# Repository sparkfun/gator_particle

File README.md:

SparkFun gator:particle - micro:bit Accessory Board
=============================

[*SparkFun gator:particle - micro:bit Accessory Board (SEN-15271)*](https://www.sparkfun.com/products/15271)

An I<sup>2</sup>C sensor for detecting particles. Additionaly, the MAX30102 sensor can also be used for measure heart-rate and SpO<sub>2</sub> using special algorithms. These algorithms have limited functionality and are primarily meant for demonstration purposed.

*Example of pulse measurement:*

Instead of using pin connections or requiring soldering, this product provides connection pads for a more kid freindly experience with alligator clips. The design intention of this product is to be used with the [gato:bit (v2)](https://www.sparkfun.com/products/15162), and the [micro:bit development board](https://www.sparkfun.com/products/14208).

Repository Contents
-------------------

* **/Hardware** - Eagle design files (.brd, .sch)
* **/Production** - Production panel files (.brd)

Documentation
--------------
* **[Hookup Guide](https://learn.sparkfun.com/tutorials/sparkfun-gatorparticle-hookup-guide)** - Basic hookup guide for the gator:particle.
* **[gator:particle PXT Package](https://github.com/sparkfun/pxt-gator-particle)** - PXT- package for the MakeCode gator:particle extension.

License Information
-------------------

This product is _**open source**_! 

Please review the LICENSE.md file for license information. 

If you have any questions or concerns on licensing, please visit the [SparkFun Forum](https://forum.sparkfun.com/index.php) and post a topic. For more general questions related to our gator boards, please visit this section of the forum: [Gator Products](https://forum.sparkfun.com/viewforum.php?f=162).

Distributed as-is; no warranty is given.

- Your friends at SparkFun.

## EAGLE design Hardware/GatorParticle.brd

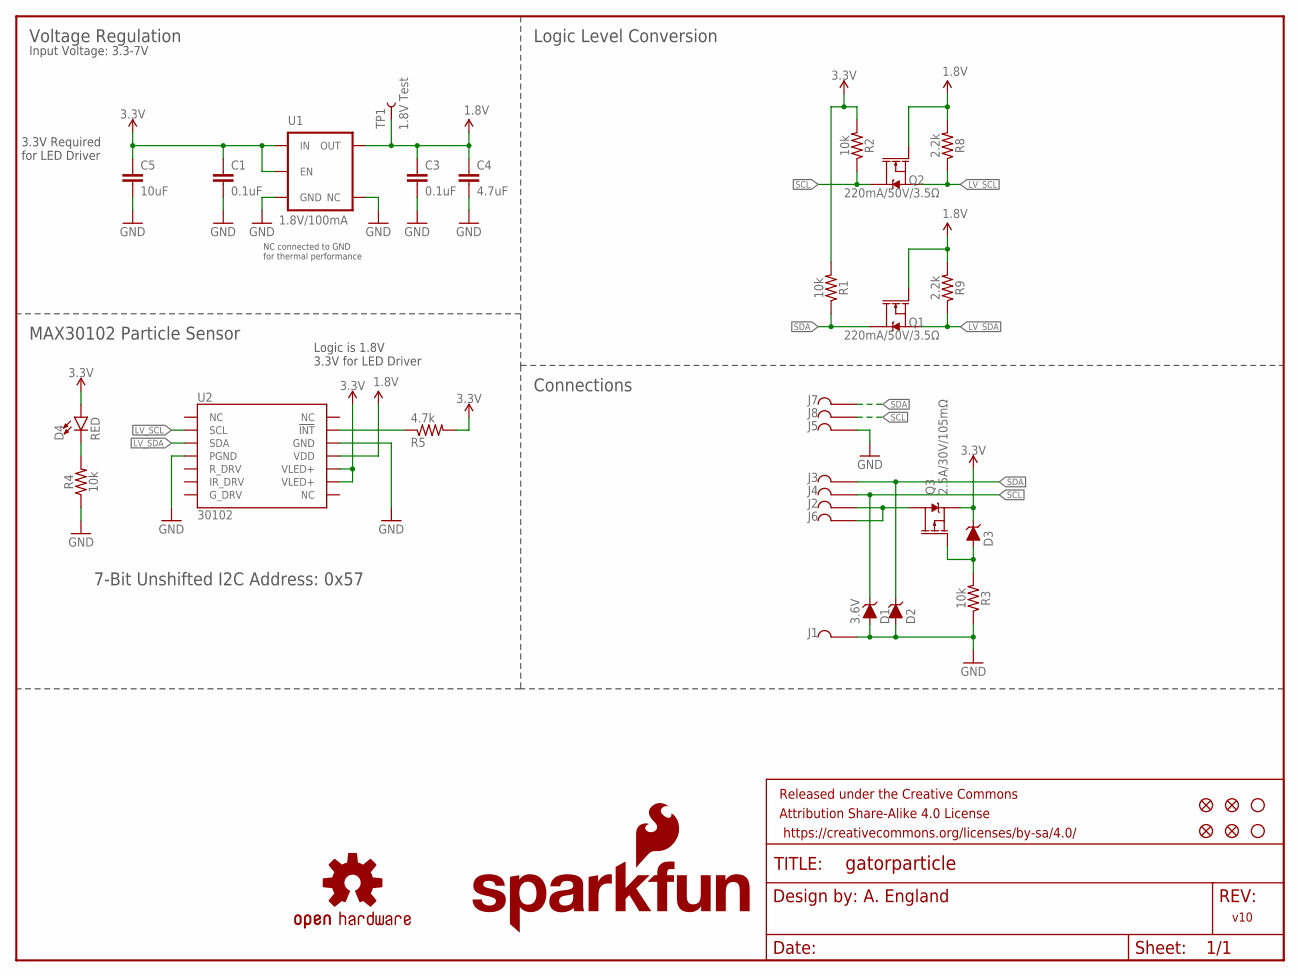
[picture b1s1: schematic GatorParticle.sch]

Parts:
C1, C3: 0.1uF; 0603
C4: 4.7uF; 0603
C5: 10uF; 0603
D1, D2, D3: 3.6V; SOD-323
D4: RED; LED-0603
FID1, FID2, FID3, FID4: FIDUCIALUFIDUCIAL; FIDUCIAL-MICRO
FRAME1: FRAME-LETTER; CREATIVE_COMMONS
J1, J2, J3, J4, J5, J6, J7, J8: GATORGATOR_MINI; GATOR_MINI
LOGO1: SFE_LOGO_NAME_FLAME.1_INCH; SFE_LOGO_NAME_FLAME_.1
LOGO2: OSHW-LOGOS; OSHW-LOGO-S
Q1, Q2: 220mA/50V/3.5Ω; SOT23-3
Q3: 2.5A/30V/105mΩ; SOT23-3
R1, R2, R3, R4: 10k; 0603
R5: 4.7k; 0603
R8, R9: 2.2k; 0603
STANDOFF2, STANDOFF3: STAND-OFFTIGHT; STAND-OFF-TIGHT
TP1: 1.8V Test; PAD.03X.04
U1: 1.8V/100mA; SC70
U2: 30102; OLGA-14

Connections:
1.8V: C3.1, C4.1, Q1.1 (G), Q2.1 (G), R8.2, R9.2, TP1.P$1, U1.5 (OUT), U2.11 (VDD)
3.3V: C1.1, C5.1, D3.C, D4.A, Q3.2 (S), R1.2, R2.2, R5.2, U1.1 (IN), U1.3 (EN), U2.9 (VLED+), U2.10 (VLED+)
!INT: R5.1, U2.13 (!INT)
GND: C1.2, C3.2, C4.2, C5.2, D1.A, D2.A, J1.P$2, J5.P$2, R3.1, R4.1, U1.2 (GND), U1.4 (NC), U2.4 (PGND), U2.12 (GND)
LV_SCL: Q2.2 (S), R8.1, U2.2 (SCL)
LV_SDA: Q1.2 (S), R9.1, U2.3 (SDA)
unnamed: D3.A, Q3.1 (G), R3.2
unnamed: J2.P$2, J6.P$2, Q3.3 (D)
unnamed: D4.C, R4.2
SCL: D1.C, J4.P$2, J8.P$2, Q2.3 (D), R2.1
SDA: D2.C, J3.P$2, J7.P$2, Q1.3 (D), R1.1

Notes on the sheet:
7-Bit Unshifted I2C Address: 0x57
v10
A. England
Voltage Regulation
Connections
MAX30102 Particle Sensor
3.3V Required for LED Driver
Logic is 1.8V 3.3V for LED Driver
NC connected to GND for thermal performance
Input Voltage: 3.3-7V
Logic Level Conversion

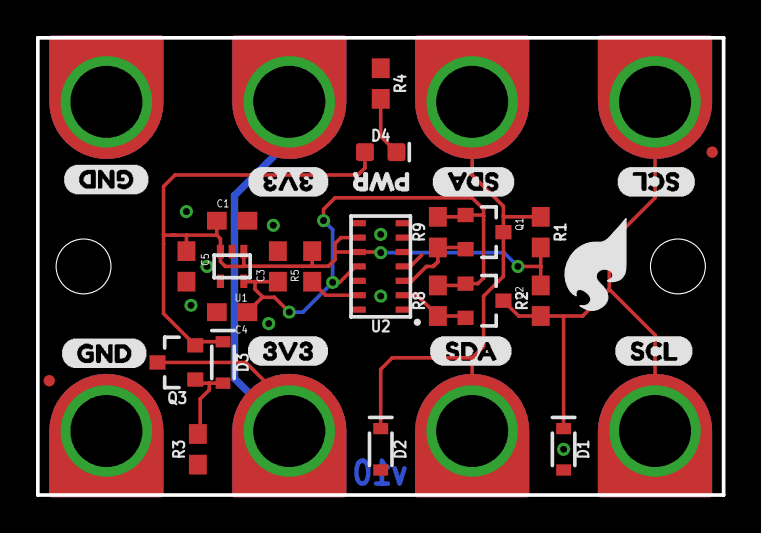
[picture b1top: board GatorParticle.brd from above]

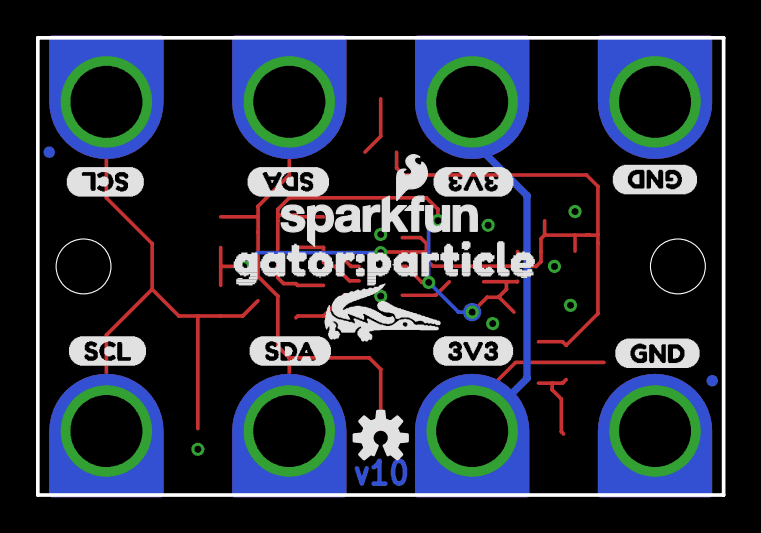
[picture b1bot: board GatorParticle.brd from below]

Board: 2 copper layers, 38.1 x 25.4 mm, 59 parts (15 on the bottom side), 11 nets.

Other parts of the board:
U$1, U$5, U$9, U$13: GND0
U$2, U$6, U$10, U$14: 3V33
U$3, U$7, U$11, U$15: SDA2
U$4, U$8, U$12, U$16: SCL1
U$17: SFE_LOGO_FLAME_.2
U$18: ORDERING_INSTRUCTIONS
U$19: PWR0
U$21: GATORBIT_FINAL_FOR_SILK#01#PNG
U$22: GATOR#PARTICLE0

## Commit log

2019-02-25 inital commit
2019-02-27 adding silk labelling
2019-02-28 adding protection circuitry
2019-02-28 finalizing silk and schematic before design review
2019-03-01 engineer run of checklist
2019-03-01 forgot to save changes from review/checklist
2019-03-12 Post checklist changes
2019-04-16 pre design review reds
2019-04-22 qc double check changes
2019-06-12 Update to current product information
    Will need to update forum link and description
2019-06-12 Rename readme.md to README.md
2019-06-12 Update
    Troubleshooting link and product description
2019-06-12 Update
    Add caption to image
2019-06-14 cleaning repo

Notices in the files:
parts and their libraries:
SparkFun-Aesthetics: Licensing: CC v3.0 Share-Alike You are welcome to use this library for commercial purposes.
SparkFun-Aesthetics: Released under the Creative Commons Attribution Share-Alike 4.0 License
SparkFun-Aesthetics: https://creativecommons.org/licenses/by-sa/4.0
